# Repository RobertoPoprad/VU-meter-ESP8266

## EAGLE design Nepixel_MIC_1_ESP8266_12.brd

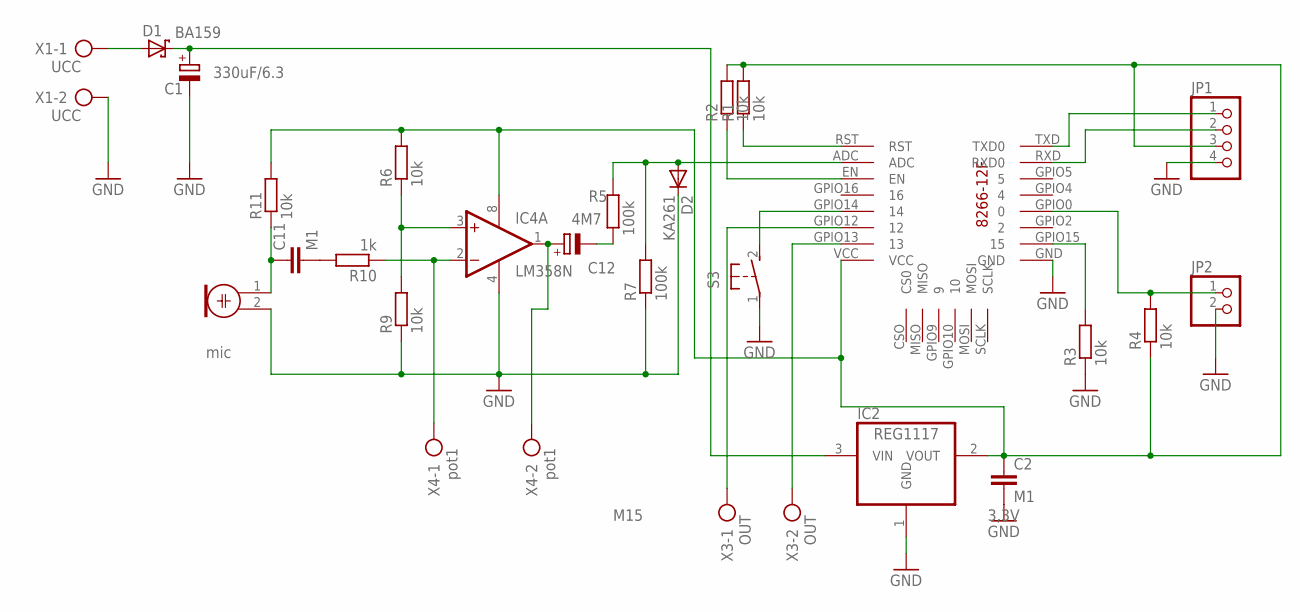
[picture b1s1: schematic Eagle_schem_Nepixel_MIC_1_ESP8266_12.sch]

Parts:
C1: 330uF/6.3; E2,5-7
C2, C11: M1; C025-024X044
C12: 4M7; E2,5-5
D1: BA159; DO35-7
D2: KA261; DO41-7.6
IC2: REG1117; SOT223
IC4: LM358N; DIL08
JP1: PINHD-1X4; 1X04
JP2: PINHD-1X2; 1X02
M1: mic; WM-64PN
R1, R2, R3, R4, R6, R9, R11: 10k; 0204/7
R5, R7: 100k; 0204/7
R10: 1k; 0204/7
S3: 31-XX; B3F-31XX
U$1: ESP826612F
X1: UCC; AK550/2
X3: OUT; AK550/2
X4: pot1; AK550/2

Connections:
GND: C1.-, C2.2, D2.C, IC2.1 (GND), IC4.4 (V-), JP1.4, JP2.2, M1.2, R3.1, R7.1, R9.1, S3.1, U$1.GND, X1.2
unnamed: D1.A, X1.1
unnamed: S3.2 (S), U$1.GPIO14 (14)
unnamed: JP1.1, U$1.TXD (TXD0)
unnamed: JP1.2, U$1.RXD (RXD0)
unnamed: JP2.1, R4.2, U$1.GPIO0 (0)
unnamed: U$1.GPIO13 (13), X3.2
unnamed: R1.1, U$1.RST
unnamed: U$1.GPIO12 (12), X3.1
unnamed: R2.1, U$1.EN
unnamed: R3.2, U$1.GPIO15 (15)
unnamed: C12.-, R5.1
unnamed: C1.+, D1.C, IC2.3 (VIN)
unnamed: C2.1, IC2.2 (VOUT), IC4.8 (V+), JP1.3, R1.2, R2.2, R4.1, R6.2, R11.2, U$1.VCC
unnamed: IC4.2 (-IN), R10.1, X4.1
unnamed: IC4.3 (+IN), R6.1, R9.2
unnamed: C11.2, R10.2
unnamed: C11.1, M1.1, R11.1
unnamed: D2.A, R5.2, R7.2, U$1.ADC
unnamed: C12.+, IC4.1 (OUT), X4.2

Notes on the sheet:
mic
M15
3,3V

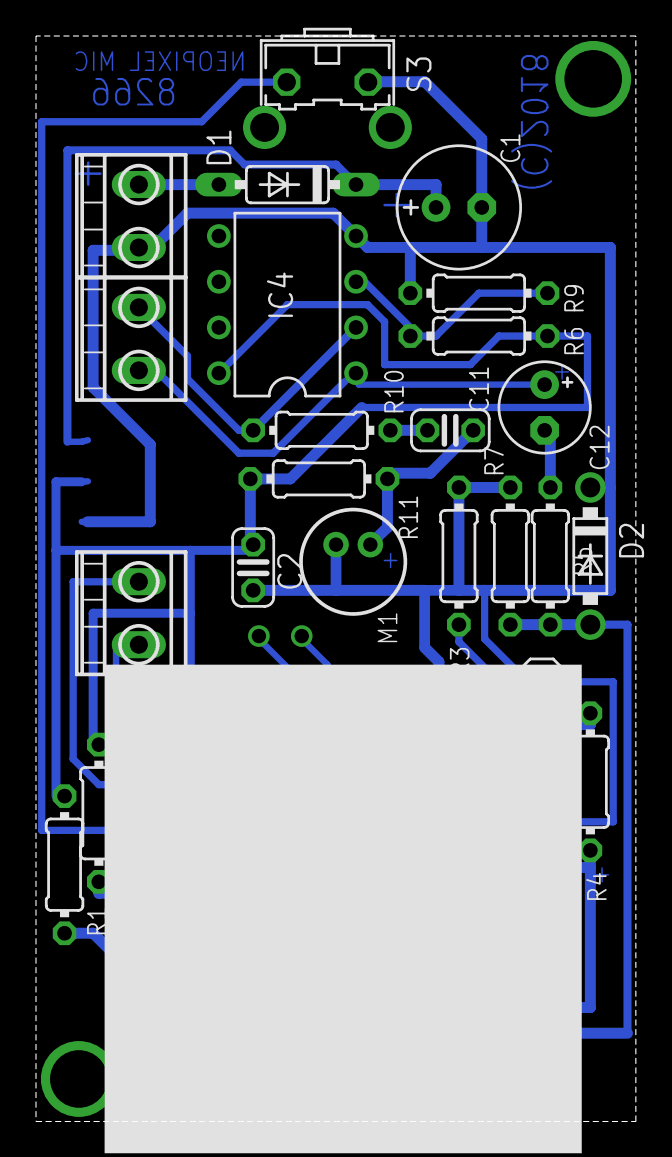
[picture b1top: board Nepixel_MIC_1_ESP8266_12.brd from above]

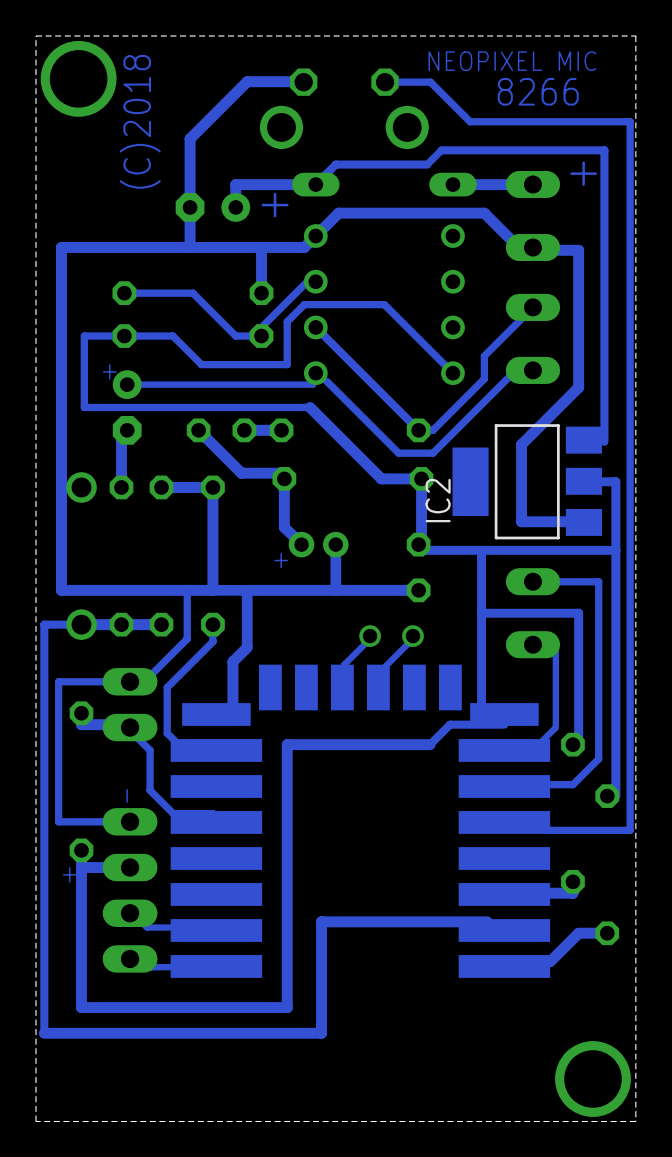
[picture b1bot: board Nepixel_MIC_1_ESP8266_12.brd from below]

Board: 2 copper layers, 33.3 x 60.3 mm, 26 parts (2 on the bottom side), 20 nets.

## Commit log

2020-03-18 Create Eagle
2020-03-18 Rename Nepixel_MIC_1_ESP8266_12.brd to Eagle_SCHEM_Nepixel_MIC_1_ESP8266_12.brd
2020-03-18 Rename Nepixel_MIC_1_ESP8266_12.sch to Eagle_schem_Nepixel_MIC_1_ESP8266_12.sch
2020-03-18 Rename Eagle_SCHEM_Nepixel_MIC_1_ESP8266_12.brd to Eagle_bard_Nepixel_MIC_1_ESP8266_12.brd

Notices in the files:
Nepixel_MIC_1_ESP8266_12.brd:
(C)2018
